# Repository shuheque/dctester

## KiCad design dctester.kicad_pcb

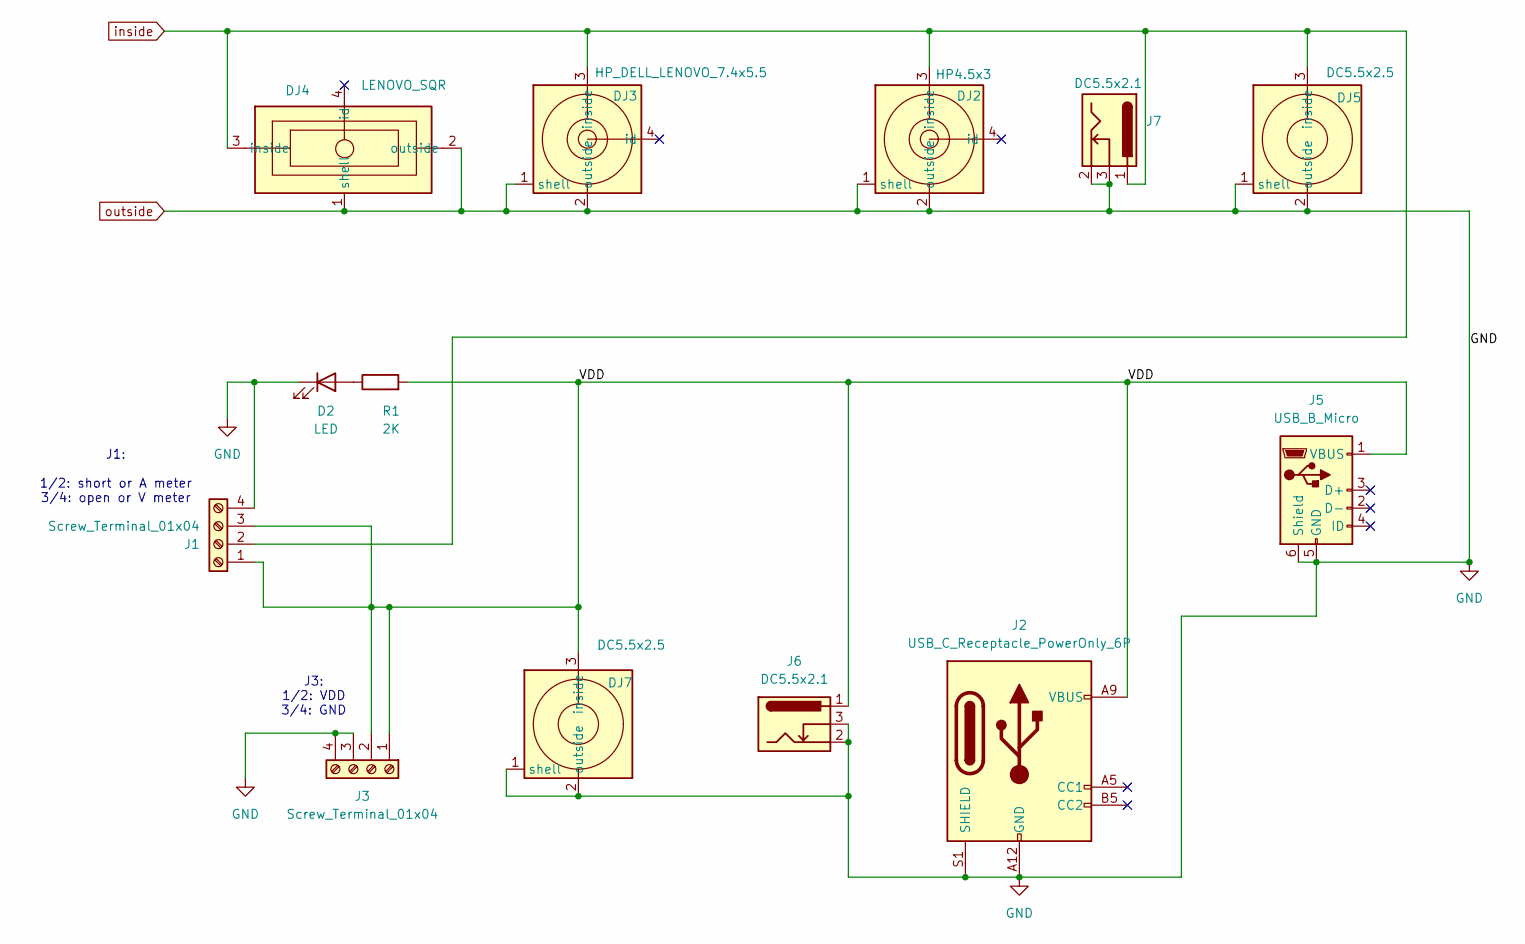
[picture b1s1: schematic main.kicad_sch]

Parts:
D2: LED; LED_D5.0mm
DJ2: HP4.5x3; hp_4.5x3.0mm_dc
DJ3: HP_DELL_LENOVO_7.4x5.5; lenovo_hp_dell_7.4x5mm_dc
DJ4: LENOVO_SQR; lenovo_square_dc
DJ5, DJ7: DC5.5x2.5; general_5.5x2.5mm_dc
J1, J3: Screw_Terminal_01x04; screw762
J2: USB_C_Receptacle_PowerOnly_6P; USB_C_Receptacle_GCT_USB4125-xx-x-0190_6P_TopMnt_Horizontal
J5: USB_B_Micro; USB_Micro-B_flat_horizon
J6, J7: DC5.5x2.1; BarrelJack_Horizontal
R1: 2K; R_Axial_DIN0207_L6.3mm_D2.5mm_P10.16mm_Horizontal

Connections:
/main/VDD: DJ7.3 (inside), J1.1, J1.3, J2.A9 (VBUS), J2.B9 (VBUS), J3.1, J3.2, J5.1 (VBUS), J6.1, R1.2
unnamed: D2.2 (A), R1.1
inside: DJ2.3 (inside), DJ3.3 (inside), DJ4.3 (inside), DJ5.3 (inside), J1.2, J7.1
outside: D2.1 (K), DJ2.1 (shell), DJ2.2 (outside), DJ3.1 (shell), DJ3.2 (outside), DJ4.1 (shell), DJ4.2 (outside), DJ5.1 (shell), DJ5.2 (outside), DJ7.1 (shell), DJ7.2 (outside), J1.4, J2.A12 (GND), J2.B12 (GND), J2.S1 (SHIELD), J3.3, J3.4, J5.5 (GND), J5.6 (Shield), J6.2, J6.3, J7.2, J7.3

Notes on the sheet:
J3: 1/2: VDD 3/4: GND
J1: 1/2: short or A meter 3/4: open or V meter

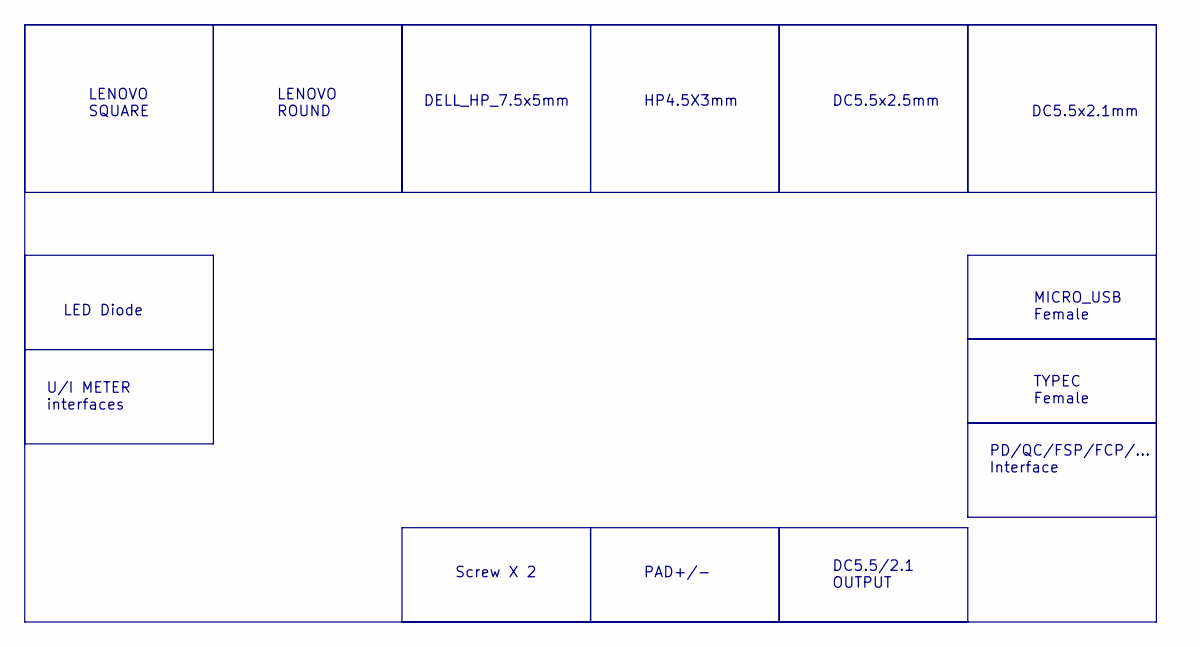
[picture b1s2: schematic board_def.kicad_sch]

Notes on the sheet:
DC5.5x2.5mm
DELL_HP_7.5x5mm
DC5.5x2.1mm
LED Diode
DC5.5/2.1 OUTPUT
MICRO_USB Female
Screw X 2
LENOVO SQUARE
U/I METER interfaces
PD/QC/FSP/FCP/... Interface
TYPEC Female
PAD+/-
HP4.5X3mm
LENOVO ROUND

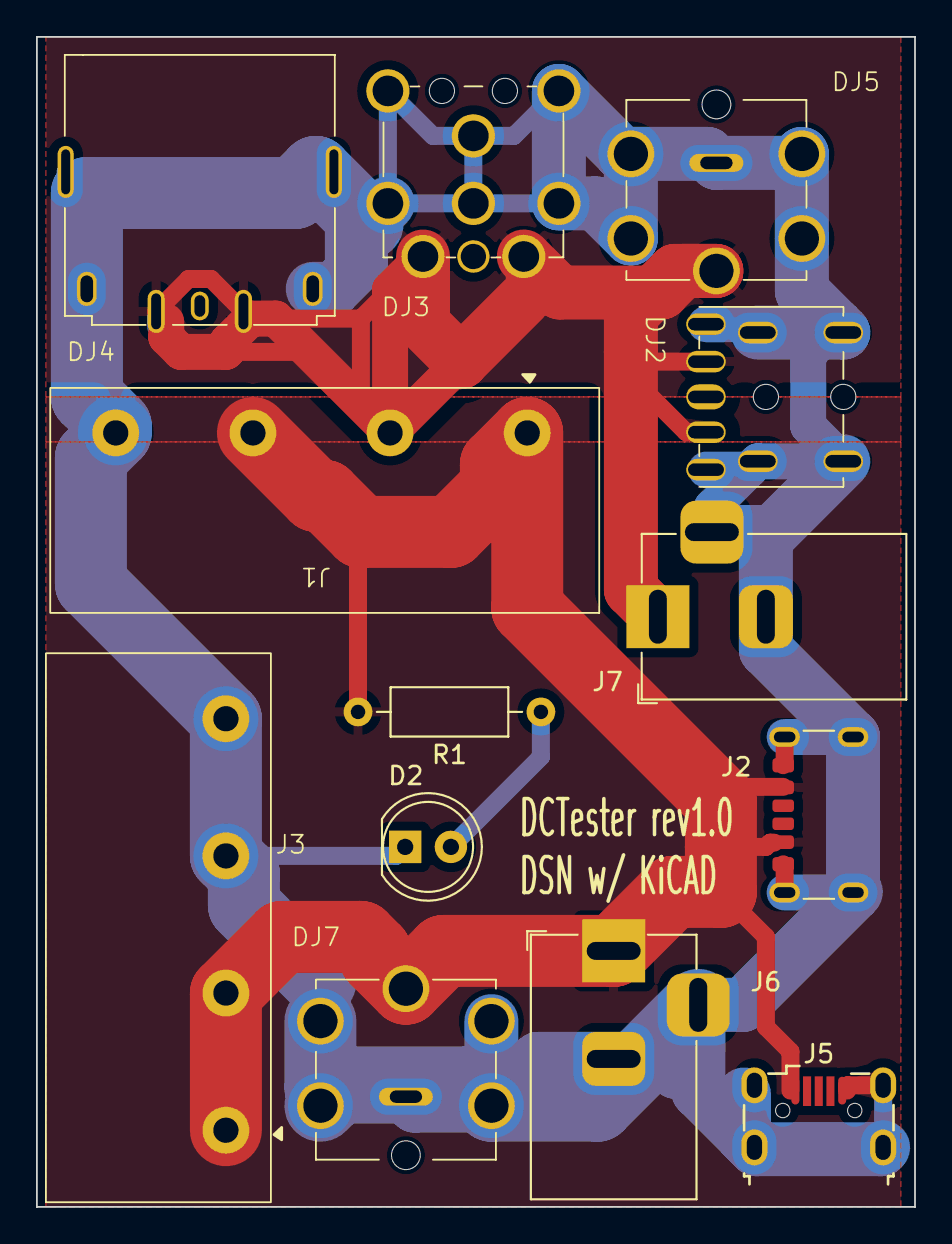
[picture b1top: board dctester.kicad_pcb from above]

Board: 2 copper layers, 48.8 x 65.0 mm, 13 parts (0 on the bottom side), 4 nets.

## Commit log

2024-12-06 init version
2024-12-10 more
2024-12-12 latest
2024-12-12 submod of libs
2024-12-12 add local libs
2024-12-12 move ptr
2024-12-12 ignore
2024-12-12 Fix DRC
2024-12-13 Fix board and DRC
2024-12-14 rev1.0
2025-05-07 add TODO
